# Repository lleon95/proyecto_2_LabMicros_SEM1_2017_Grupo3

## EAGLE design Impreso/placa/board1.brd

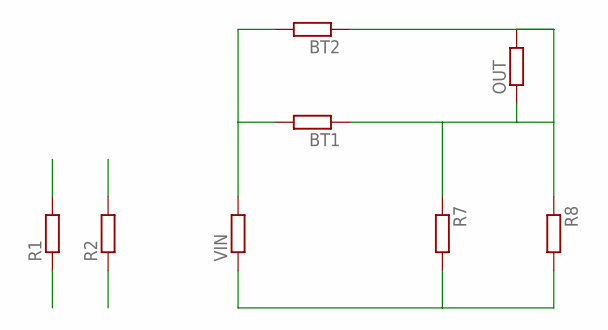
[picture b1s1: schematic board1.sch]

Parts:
BT1, BT2: R-EU_0204/2V; 0204V
OUT: R-EU_0204/5; 0204/5
R1, R2, R7, R8: R-EU_0204/2V; 0204V
VIN: R-EU_0204/2V; 0204V

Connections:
CLKI: R2.2
CLKO: R2.1
DTI: R1.2
DTO: R1.1
GROUND: R7.2, R8.2, VIN.1
unnamed: BT1.2, BT2.2, VIN.2
unnamed: BT1.1, OUT.1, R7.1
unnamed: BT2.1, OUT.2, R8.1

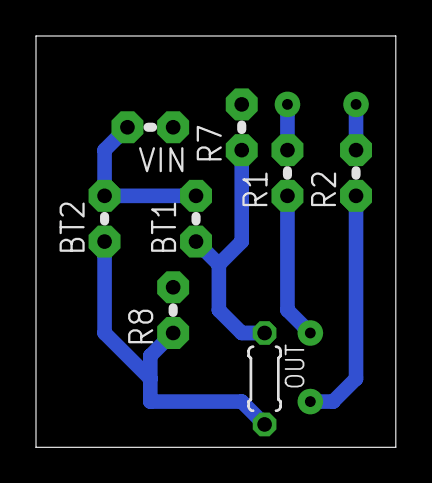
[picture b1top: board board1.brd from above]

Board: 2 copper layers, 20.0 x 22.9 mm, 8 parts (0 on the bottom side), 4 nets.

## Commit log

2017-05-02 :neckbeard: Added .gitattributes & .gitignore files
2017-05-03 Generar datos
2017-05-06 ENlaces del SO
2017-05-06 Codigo de prueba
2017-05-06 Termina del lectura de datos
2017-05-08 Enlaces
2017-05-09 filter update
2017-05-10 Main y sender de prueba estable
2017-05-10 Mediciones Hyst
2017-05-10 Hystheresis
2017-05-10 Driver listo y estable
2017-05-10 Opcion para seleccionar el puerto serial
2017-05-11 Actualizar main.py
2017-05-11 Correcciones. Poner Try and Excepts
2017-05-12 Funcional pero no estable
2017-05-12 Ultimos funcionales, pero no estables
2017-05-12 Agregar codigo de prueba en RAW
2017-05-12 Hola
2017-05-12 Implementacion con Linear Regression
2017-05-13 Script linear regression final
2017-05-14 Nuevo Driver
2017-05-14 Corregir desplazamiento
2017-05-14 Corregir
2017-05-14 Agregar ping
2017-05-14 Corregir puertos
2017-05-14 Corregir bug de variable dx instead dy
2017-05-14 escalar
2017-05-14 Reducir escalamiento aditivo
2017-05-14 aumentar el baudrate
2017-05-14 Incorporar clics
2017-05-17 Actualizar baudrate y quitar datos erroneos
